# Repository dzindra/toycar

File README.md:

# WiFi controlled toy car

Made as a present for my friend's birthday 

* ESP-8266 with NodeMCU
* L293 dual H-bridge driver
* Small geared DC motors
* Pololu wheels and idler
* 3D printed case
* iOS app for car control

## Photos

## Schematic and PCB

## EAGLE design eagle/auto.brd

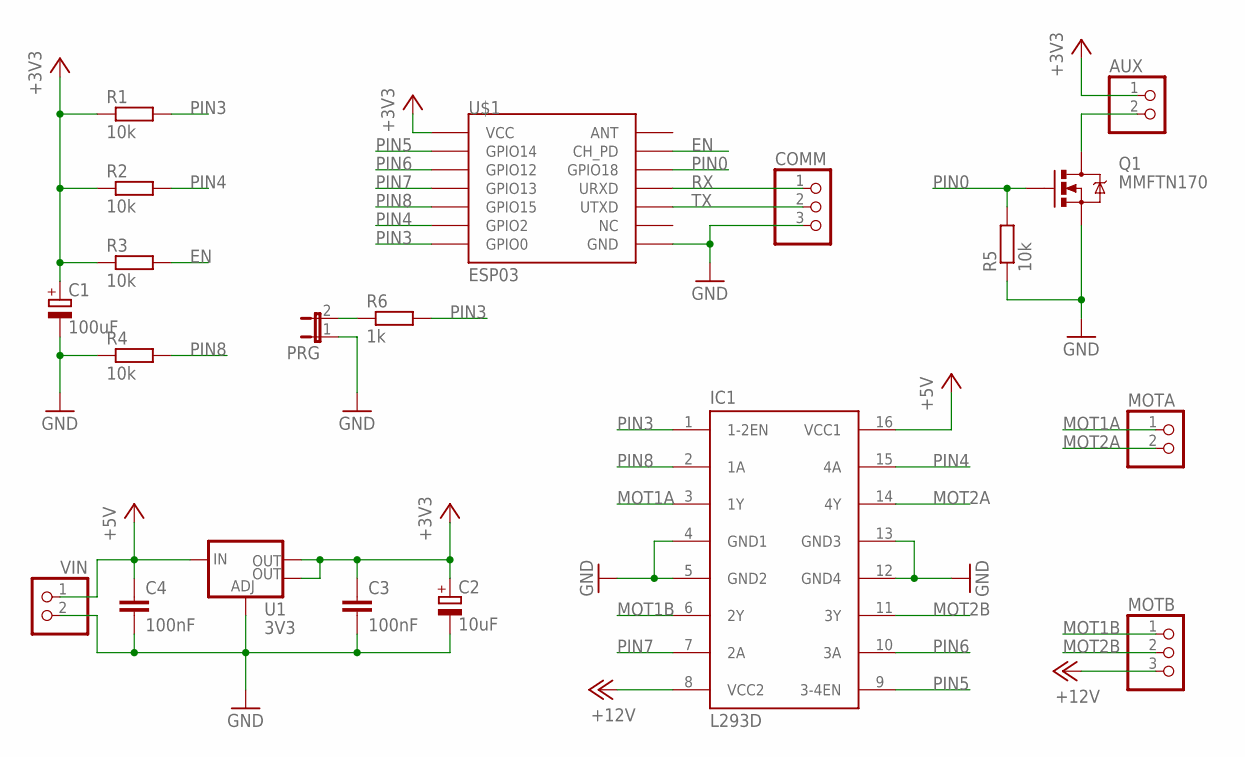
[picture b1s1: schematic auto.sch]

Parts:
AUX: PINHD-1X2; 1X02
C1: 100uF; E2,5-5
C2: 10uF; E2,5-5
C3, C4: 100nF; C1206
COMM: PINHD-1X3; 1X03
IC1: L293D; DIL16
MOTA: PINHD-1X2; 1X02
MOTB: PINHD-1X3; 1X03
PRG: JP1E; JP1
Q1: MMFTN170; SOT23-3
R1, R2, R3, R4, R5: 10k; R0805
R6: 1k; R0805
U1: 3V3; SOT223
U$1: ESP03
VIN: PINHD-1X2; 1X02

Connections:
+3V3: AUX.1, C1.+, C2.+, C3.1, R1.1, R2.1, R3.1, U1.2 (OUT), U1.4 (OUT), U$1.VCC
+5V: C4.1, IC1.16 (VCC1), U1.3 (IN), VIN.1
+12V: IC1.8 (VCC2), MOTB.3
EN: R3.2, U$1.CH_PD
GND: C1.-, C2.-, C3.2, C4.2, COMM.3, IC1.4 (GND1), IC1.5 (GND2), IC1.12 (GND4), IC1.13 (GND3), PRG.1, Q1.2 (S), R4.1, R5.1, U1.1 (ADJ), U$1.GND, VIN.2
MOT1A: IC1.3 (1Y), MOTA.1
MOT1B: IC1.6 (2Y), MOTB.1
MOT2A: IC1.14 (4Y), MOTA.2
MOT2B: IC1.11 (3Y), MOTB.2
unnamed: AUX.2, Q1.3 (D)
unnamed: PRG.2, R6.1
PIN0: Q1.1 (G), R5.2, U$1.GPIO18
PIN3: IC1.1 (1-2EN), R1.2, R6.2, U$1.GPIO0
PIN4: IC1.15 (4A), R2.2, U$1.GPIO2
PIN5: IC1.9 (3-4EN), U$1.GPIO14
PIN6: IC1.10 (3A), U$1.GPIO12
PIN7: IC1.7 (2A), U$1.GPIO13
PIN8: IC1.2 (1A), R4.2, U$1.GPIO15
RX: COMM.1, U$1.URXD
TX: COMM.2, U$1.UTXD

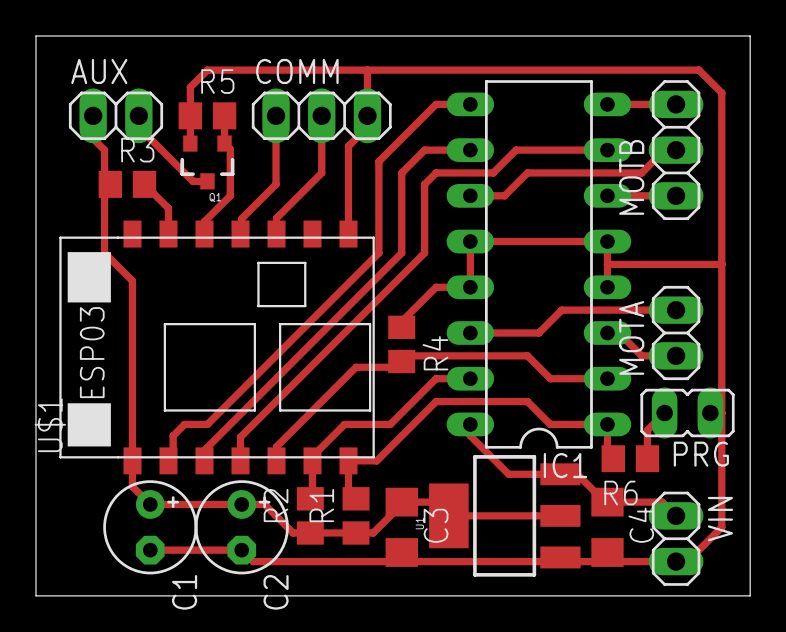
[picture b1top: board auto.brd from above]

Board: 2 copper layers, 39.7 x 31.1 mm, 20 parts (0 on the bottom side), 20 nets.

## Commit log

2016-04-10 Add schematic and board layout
2016-04-10 Add 3D models
2016-04-10 Add ESP8266 lua sources
2016-04-10 Add iOS app
2016-04-10 Add images

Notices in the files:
parts and their libraries:
SparkFun-PowerIC: Licensing: Creative Commons ShareAlike 4.0 International - https://creativecommons.org/licenses/by-sa/4.0
